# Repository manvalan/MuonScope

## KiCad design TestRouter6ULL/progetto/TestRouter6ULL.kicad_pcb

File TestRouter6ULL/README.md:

# TestRouter6ULL: scheda minima i.MX 6ULL + DDR3L per provare lo sbroglio con BoardLab

Scheda di prova **solo placement, nessuna pista**: tutte le connessioni sono lasciate all'autorouter. Aprire `progetto/TestRouter6ULL.kicad_pro`.

| | |
|---|---|
| Scheda | 60 x 50 mm, angoli raggiati 3 mm, 4 fori M2 con keepout |
| Strati | 4 (F.Cu, In1.Cu GND, In2.Cu PWR, B.Cu), stackup standard PCBWay come ProvaDDR |
| Componenti | 89 (65 top, 24 bottom) + 4 fori |
| Net | 84 (44 classe `DDR`, 6 classe `DDR_DIFF`, 34 `Default`) |
| ERC | 0 errori, 0 avvisi |
| DRC | 0 violazioni, 0 problemi di parita' schema/PCB, 349 connessioni non sbrogliate (attese) |

File: `schema-testrouter6ull.pdf` (schema), `placement-testrouter6ull.png` (top a sinistra, bottom specchiato a destra).

## Contenuto

- **U1** NXP MCIMX6Y2CVM08AB, MAPBGA-289 14x14 passo 0.8. Mappa delle sfere da SchedaIMX6ULL-SD (IMX6ULLCEC Rev 1.2, tabelle 90/91). Collegati solo DDR, alimentazioni, clock, reset, boot e UART1; le altre sfere hanno il no_connect.
- **U2** Micron MT41K512M16HA-107:A, DDR3L x16 1 GB, FBGA-96 9x14 passo 0.8. **AS4C512M16D3LC non c'e' nella libreria MIKILAB**: uso il Micron, stessa ball map JEDEC x16 e stesso footprint, quindi si puo' montare l'Alliance senza modifiche. Simbolo: MT41K256M16HA di KiCad con A15 su M7.
- Bus DDR completo SoC-DRAM: DQ0-15, LDQS/UDQS P/N, LDM/UDM, A0-A15, BA0-2, CK P/N, CKE, CS#, RAS#, CAS#, WE#, ODT, RESET#. ZQ 240R 1% su SoC e DRAM, VREF a partitore 1k/1k con 100 nF su ogni resistenza (unica per DRAM_VREF, VREFCA, VREFDQ), 10k a GND su RESET# e CKE, 100R tra CK_P e CK_N vicino alla DRAM.
- Disaccoppiamento di SoC e DDR come SchedaIMX6ULL-SD, tutto 0603 o piu' grande: 17 condensatori sul bottom sotto e accanto alle BGA (8 sotto U1, 4 sotto U2, 5 sui rail `_CAP` vicino all'angolo basso destro di U1).
- Y1 24 MHz (X322524MOB4SI) con 2x18 pF, Y2 32.768 kHz (Q13FC1350000400) con 2x12 pF, sotto il SoC vicino alle sfere XTAL e RTC.
- POR_B: RC 10k/1uF dal 3.3 V. JTAG_MOD 4.7k a GND, JTAG non usato.
- BOOT_MODE[1:0] = 01 (serial downloader, la scheda non ha memorie di boot: il ROM aspetta su UART1/USB). Due resistenze DNP per passare a BOOT_MODE = 10.
- J2 console UART1 (header 3 pin: TX, RX, GND) sul bordo alto.

## Alimentazione

Scelta la soluzione con i regolatori sulla scheda (gli stessi, con gli stessi valori, di SchedaIMX6ULL-SD) invece dei rail da header: e' poco piu' complessa e la scheda resta alimentabile da sola con 5 V.

- J1 header 2 pin: 5 V e GND, sul bordo basso.
- U3 TPS563201 -> 3V3 (FB 33.2k/10k), primo della sequenza.
- U4 TLV62569 -> V1P35 per NVCC_DRAM e DDR3L (FB 150k/120k), EN 100k/470nF dal 3V3.
- U5 TLV62569 -> V1P4 per VDD_SOC_IN (FB 133k/100k = 1.398 V), EN 100k/1uF dal 3V3.
- VDD_SNVS_IN e VDD_HIGH_IN dal 3V3, niente pila.

I buck sono in colonna sul lato destro, lontani dalla DDR3L.

## Regole e classi

Stackup PCBWay 4 strati 1.6 mm (voce 1 della tabella *Multi-layer laminated structure*): prepreg 7628 0.1855 mm Er 4.74, core 1.03 mm, rame 1 oz su tutti gli strati. Identico a ProvaDDR.

Regole in `progetto/TestRouter6ULL.kicad_dru`: piste 5 mil (0.127 mm), 4 mil (0.1016 mm) sotto il courtyard di qualsiasi componente su entrambi i lati, distanza 0.1 mm, via 0.45/0.2 mm.

| Classe | Net | Pista | Distanza | Coppia |
|---|---|---|---|---|
| `DDR` | A, BA, DQ, DM e comandi (44) | 0.127 | 0.127 | |
| `DDR_DIFF` | CK, LDQS, UDQS (6) | 0.127 | 0.127 | 0.127 / gap 0.127 |
| `Default` | il resto, VREF e ZQ compresi | 0.127 | 0.1 | |

Le classi DDR sono a 5 mil, non a impedenza controllata: su questo stackup 5 mil sono circa 77 ohm singola (calcolo di ProvaDDR), 50 ohm richiederebbe 0.316 mm, che non passano tra le sfere. Per una scheda di prova dello sbroglio e' la scelta piu' semplice; per una scheda vera serve uno stackup con prepreg sottile.

## Rigenerazione

`generatori/build.sh` rigenera tutto in `progetto/` (schema, ERC, PDF, PCB, DRC, PNG). Serve KiCad 10 con il modulo Python `pcbnew`, le librerie standard di KiCad 10 e la libreria MIKILAB (`~/Develop/mikilab-kicad-library` o variabile `MIKILAB`). I generatori sono adattati da `SchedaIMX6ULL-SD/generatori` (branch `claude/project-thread-034nik`). Le posizioni dei passivi sono calcolate: ogni rigenerazione puo' spostarli di poco.

## Problemi aperti

- AS4C512M16D3LC assente dalla libreria: in schema c'e' MT41K512M16HA (compatibile pin a pin).
- Alcuni passivi lenti del SoC (boot, POR, bulk 22 uF) sono a 13-17 mm da U1, perche' la corona attorno alle BGA resta libera per il fanout.
- I resistori VREF/ZQ della DRAM sono nell'angolo basso sinistro, a 10-16 mm da U2: vanno bene per la prova del router, su una scheda vera ZQ e VREF vanno avvicinati.
- I condensatori sul bottom sotto le BGA occupano posti dove uno sbroglio con un via per sfera metterebbe i via di alimentazione: lo sbrogliatore dovra' condividerli o spostarli, come in ProvaDDR.

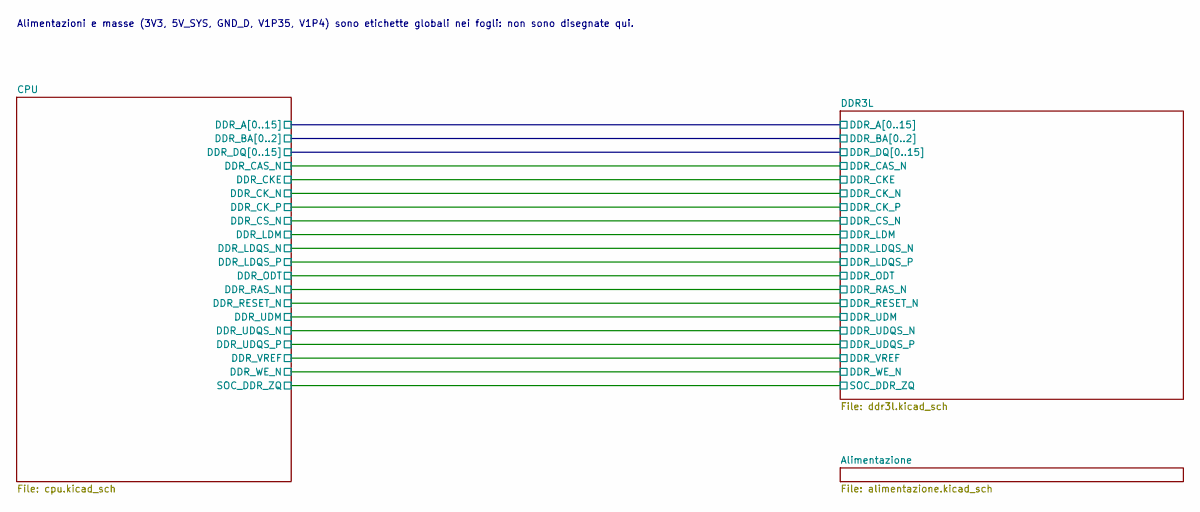
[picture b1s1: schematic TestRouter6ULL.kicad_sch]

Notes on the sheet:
Alimentazioni e masse (3V3, 5V_SYS, GND_D, V1P35, V1P4) sono etichette globali nei fogli: non sono disegnate qui.

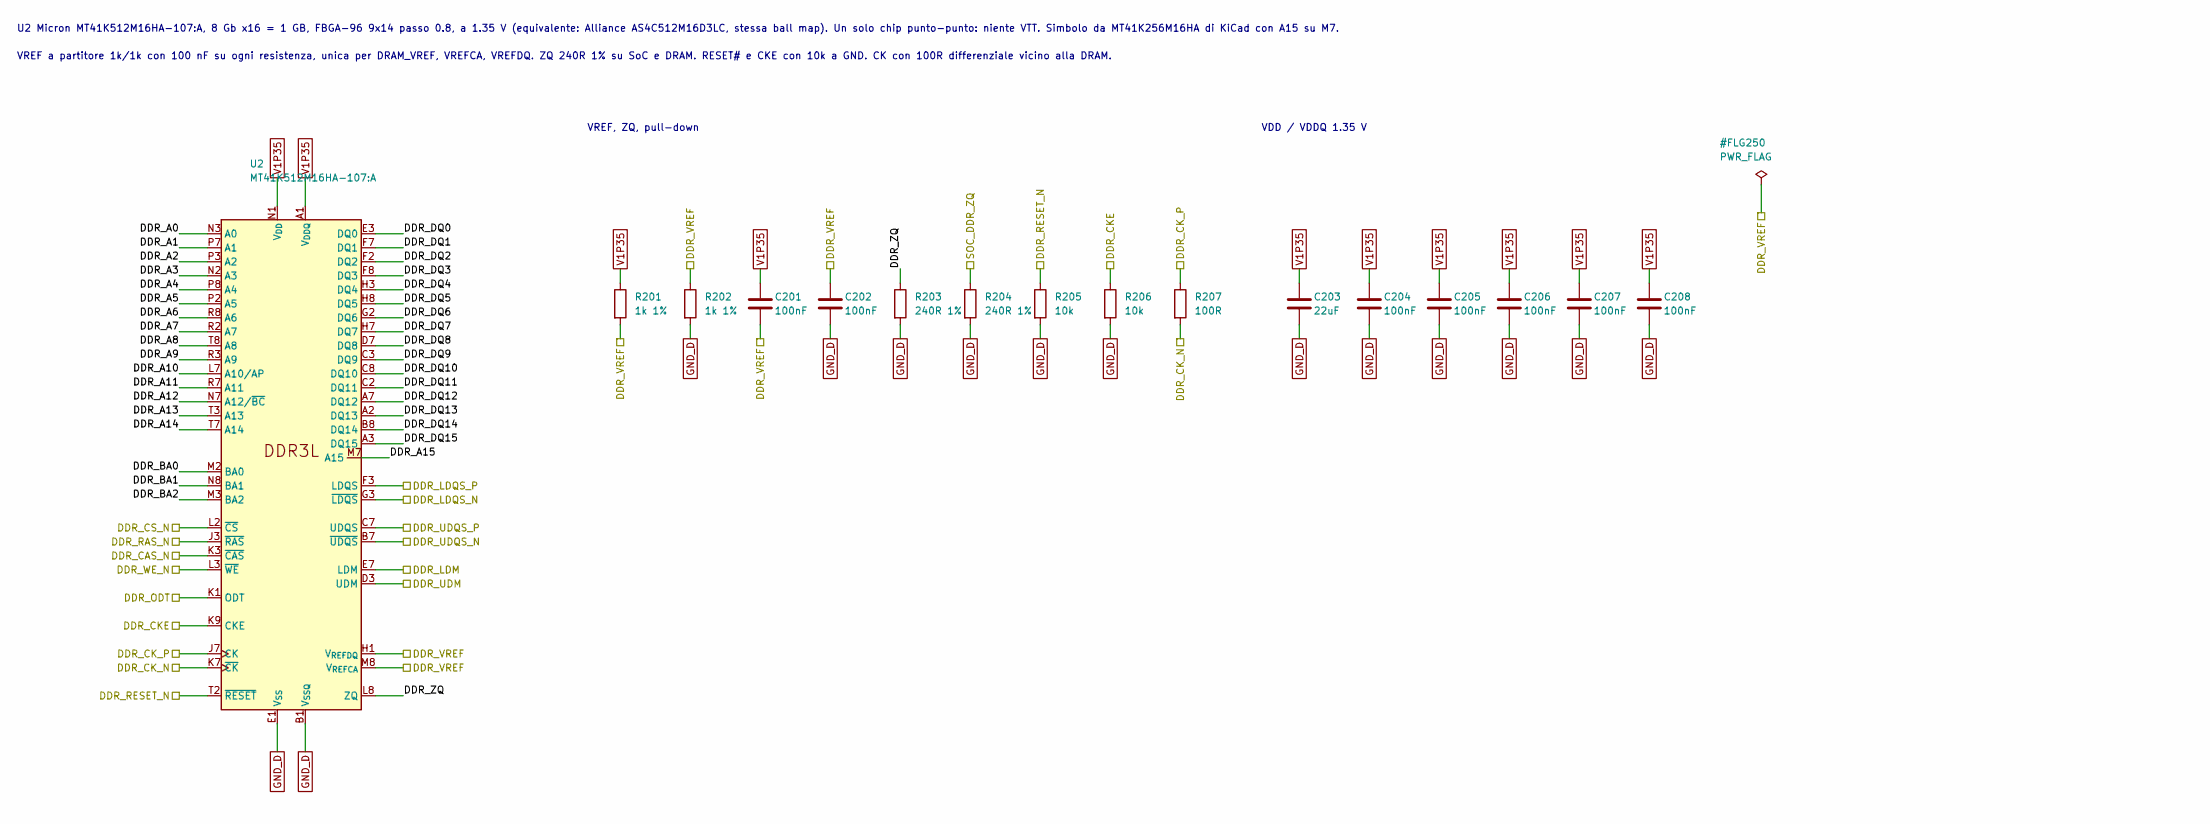
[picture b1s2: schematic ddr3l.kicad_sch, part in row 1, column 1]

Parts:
C201, C202, C204, C205, C206, C207, C208: 100nF; C_0603_1608Metric
C203: 22uF; C_0805_2012Metric
R201, R202: 1k 1%; R_0603_1608Metric
R203, R204: 240R 1%; R_0603_1608Metric
R205, R206: 10k; R_0603_1608Metric
R207: 100R; R_0603_1608Metric
U2: MT41K512M16HA-107:A; Micron_FBGA-96_9x14mm_Layout9x16_P0.8mm; MPN MT41K512M16HA-107:A

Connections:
/CPU/DDR_A0: U2.N3 (A0); also elsewhere on the board
/CPU/DDR_A1: U2.P7 (A1); also elsewhere on the board
/CPU/DDR_A2: U2.P3 (A2); also elsewhere on the board
/CPU/DDR_A3: U2.N2 (A3); also elsewhere on the board
/CPU/DDR_A4: U2.P8 (A4); also elsewhere on the board
/CPU/DDR_A5: U2.P2 (A5); also elsewhere on the board
/CPU/DDR_A6: U2.R8 (A6); also elsewhere on the board
/CPU/DDR_A7: U2.R2 (A7); also elsewhere on the board
/CPU/DDR_A8: U2.T8 (A8); also elsewhere on the board
/CPU/DDR_A9: U2.R3 (A9); also elsewhere on the board
/CPU/DDR_A10: U2.L7 (A10/AP); also elsewhere on the board
/CPU/DDR_A11: U2.R7 (A11); also elsewhere on the board
/CPU/DDR_A12: U2.N7 (A12/~BC); also elsewhere on the board
/CPU/DDR_A13: U2.T3 (A13); also elsewhere on the board
/CPU/DDR_A14: U2.T7 (A14); also elsewhere on the board
/CPU/DDR_A15: U2.M7 (A15); also elsewhere on the board
/CPU/DDR_BA0: U2.M2 (BA0); also elsewhere on the board
/CPU/DDR_BA1: U2.N8 (BA1); also elsewhere on the board
/CPU/DDR_BA2: U2.M3 (BA2); also elsewhere on the board
/CPU/DDR_CAS_N: U2.K3 (~CAS); also elsewhere on the board
/CPU/DDR_CKE: R206.1, U2.K9 (CKE); also elsewhere on the board
/CPU/DDR_CK_N: R207.2, U2.K7 (~CK); also elsewhere on the board
/CPU/DDR_CK_P: R207.1, U2.J7 (CK); also elsewhere on the board
/CPU/DDR_CS_N: U2.L2 (~CS); also elsewhere on the board
/CPU/DDR_DQ0: U2.E3 (DQ0); also elsewhere on the board
/CPU/DDR_DQ1: U2.F7 (DQ1); also elsewhere on the board
/CPU/DDR_DQ2: U2.F2 (DQ2); also elsewhere on the board
/CPU/DDR_DQ3: U2.F8 (DQ3); also elsewhere on the board
/CPU/DDR_DQ4: U2.H3 (DQ4); also elsewhere on the board
/CPU/DDR_DQ5: U2.H8 (DQ5); also elsewhere on the board
/CPU/DDR_DQ6: U2.G2 (DQ6); also elsewhere on the board
/CPU/DDR_DQ7: U2.H7 (DQ7); also elsewhere on the board
/CPU/DDR_DQ8: U2.D7 (DQ8); also elsewhere on the board
/CPU/DDR_DQ9: U2.C3 (DQ9); also elsewhere on the board
/CPU/DDR_DQ10: U2.C8 (DQ10); also elsewhere on the board
/CPU/DDR_DQ11: U2.C2 (DQ11); also elsewhere on the board
/CPU/DDR_DQ12: U2.A7 (DQ12); also elsewhere on the board
/CPU/DDR_DQ13: U2.A2 (DQ13); also elsewhere on the board
/CPU/DDR_DQ14: U2.B8 (DQ14); also elsewhere on the board
/CPU/DDR_DQ15: U2.A3 (DQ15); also elsewhere on the board
/CPU/DDR_LDM: U2.E7 (LDM); also elsewhere on the board
/CPU/DDR_LDQS_N: U2.G3 (~LDQS); also elsewhere on the board
/CPU/DDR_LDQS_P: U2.F3 (LDQS); also elsewhere on the board
/CPU/DDR_ODT: U2.K1 (ODT); also elsewhere on the board
/CPU/DDR_RAS_N: U2.J3 (~RAS); also elsewhere on the board
/CPU/DDR_RESET_N: R205.1, U2.T2 (~RESET); also elsewhere on the board
/CPU/DDR_UDM: U2.D3 (UDM); also elsewhere on the board
/CPU/DDR_UDQS_N: U2.B7 (~UDQS); also elsewhere on the board
/CPU/DDR_UDQS_P: U2.C7 (UDQS); also elsewhere on the board
/CPU/DDR_VREF: C201.2, C202.1, R201.2, R202.1, U2.H1 (V_{REFDQ}), U2.M8 (V_{REFCA}); also elsewhere on the board
/CPU/DDR_WE_N: U2.L3 (~WE); also elsewhere on the board
/CPU/SOC_DDR_ZQ: R204.1; also elsewhere on the board
/DDR3L/DDR_ZQ: R203.1, U2.L8 (ZQ)
GND_D: C202.2, C203.2, C204.2, C205.2, C206.2, C207.2, C208.2, R202.2, R203.2, R204.2, R205.2, R206.2, U2.A9 (V_{SS}), U2.B1 (V_{SSQ}), U2.B3 (V_{SS}), U2.B9 (V_{SSQ}), U2.D1 (V_{SSQ}), U2.D8 (V_{SSQ}), U2.E1 (V_{SS}), U2.E2 (V_{SSQ}), U2.E8 (V_{SSQ}), U2.F9 (V_{SSQ}), U2.G1 (V_{SSQ}), U2.G8 (V_{SS}), U2.G9 (V_{SSQ}), U2.J2 (V_{SS}), U2.J8 (V_{SS}), U2.M1 (V_{SS}), U2.M9 (V_{SS}), U2.P1 (V_{SS}), U2.P9 (V_{SS}), U2.T1 (V_{SS}), U2.T9 (V_{SS}); also elsewhere on the board
V1P35: C201.1, C203.1, C204.1, C205.1, C206.1, C207.1, C208.1, R201.1, U2.A1 (V_{DDQ}), U2.A8 (V_{DDQ}), U2.B2 (V_{DD}), U2.C1 (V_{DDQ}), U2.C9 (V_{DDQ}), U2.D2 (V_{DDQ}), U2.D9 (V_{DD}), U2.E9 (V_{DDQ}), U2.F1 (V_{DDQ}), U2.G7 (V_{DD}), U2.H2 (V_{DDQ}), U2.H9 (V_{DDQ}), U2.K2 (V_{DD}), U2.K8 (V_{DD}), U2.N1 (V_{DD}), U2.N9 (V_{DD}), U2.R1 (V_{DD}), U2.R9 (V_{DD}); also elsewhere on the board

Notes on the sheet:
U2 Micron MT41K512M16HA-107:A, 8 Gb x16 = 1 GB, FBGA-96 9x14 passo 0.8, a 1.35 V (equivalente: Alliance AS4C512M16D3LC, stessa ball map). Un solo chip punto-punto: niente VTT. Simbolo da MT41K256M16HA di KiCad con A15 su M7.
VREF a partitore 1k/1k con 100 nF su ogni resistenza, unica per DRAM_VREF, VREFCA, VREFDQ. ZQ 240R 1% su SoC e DRAM. RESET# e CKE con 10k a GND. CK con 100R differenziale vicino alla DRAM.
VREF, ZQ, pull-down
VDD / VDDQ 1.35 V

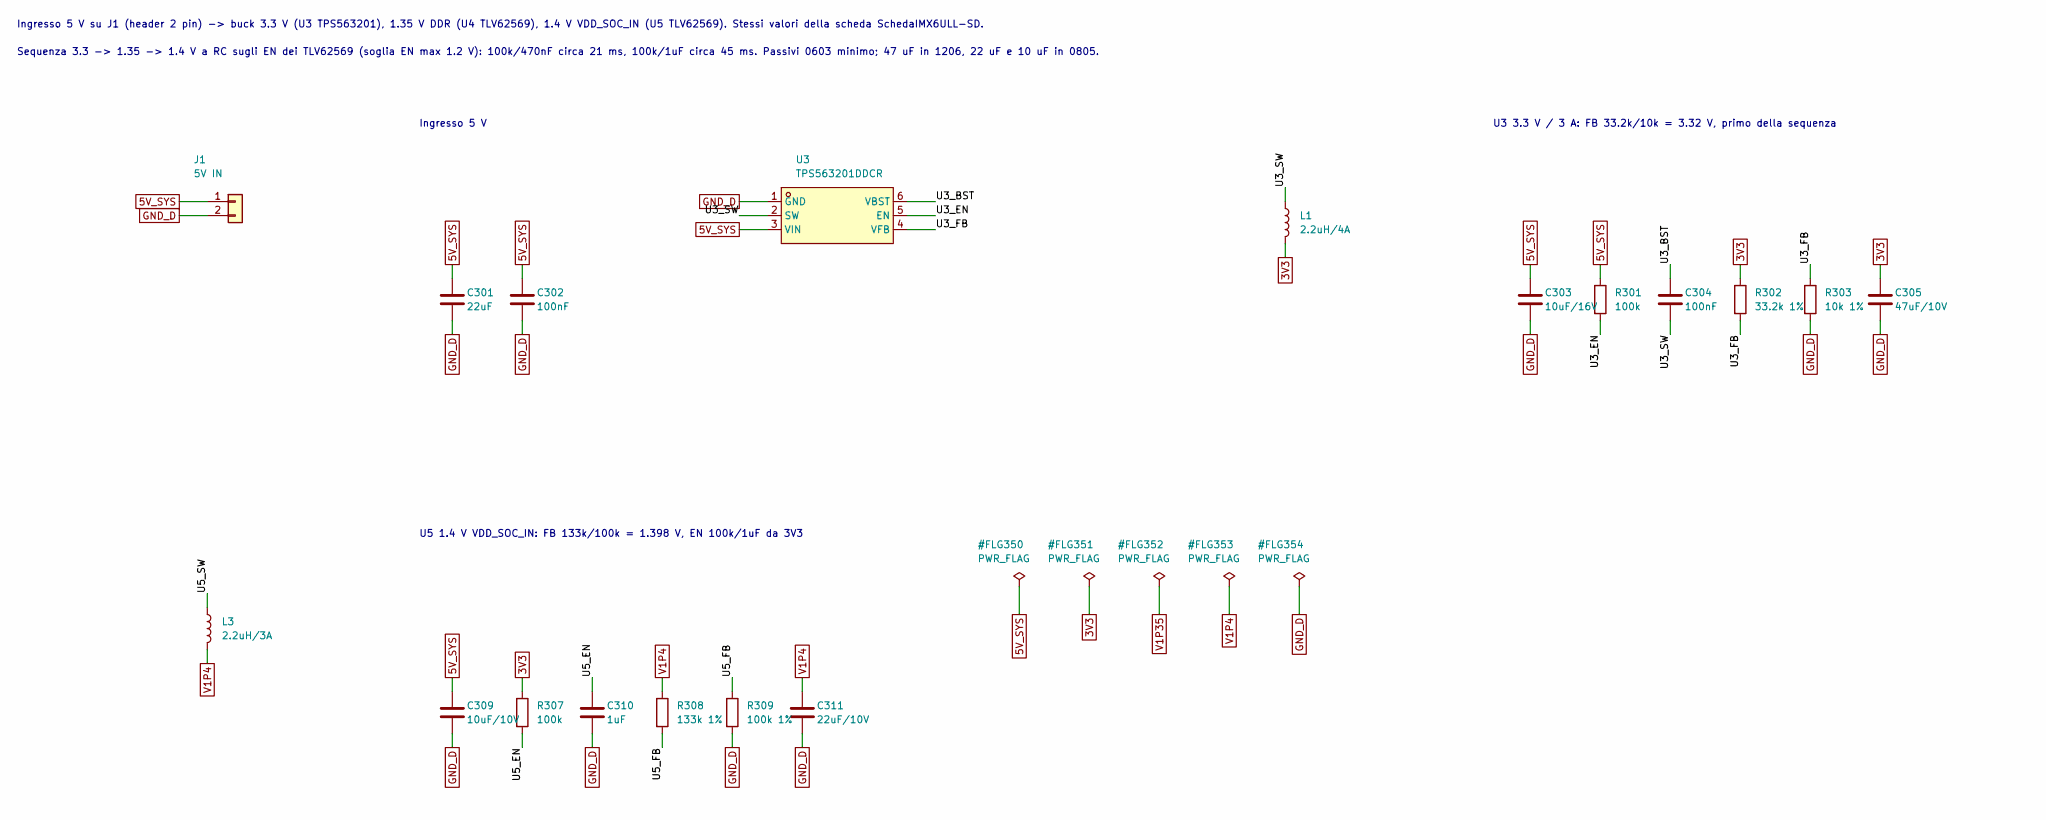
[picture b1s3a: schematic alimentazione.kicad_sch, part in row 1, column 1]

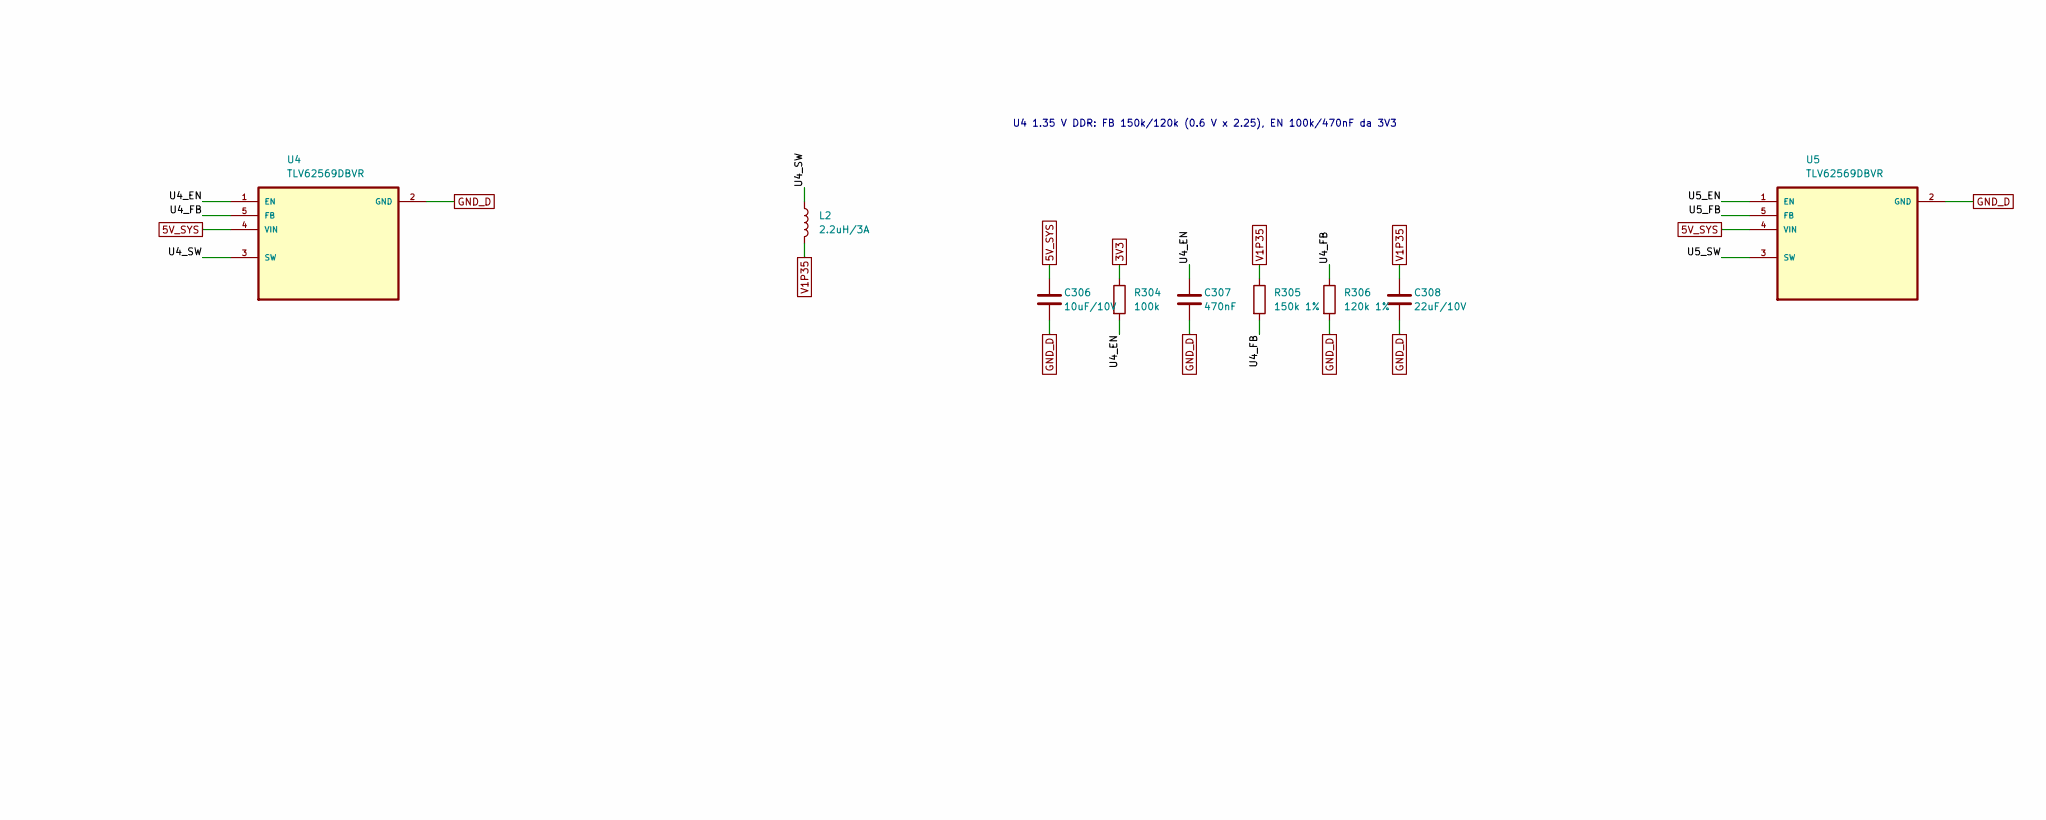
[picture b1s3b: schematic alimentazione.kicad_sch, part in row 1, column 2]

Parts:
C301: 22uF; C_1206_3216Metric
C302, C304: 100nF; C_0603_1608Metric
C303: 10uF/16V; C_0805_2012Metric
C305: 47uF/10V; C_1206_3216Metric
C306, C309: 10uF/10V; C_0805_2012Metric
C307: 470nF; C_0603_1608Metric
C308, C311: 22uF/10V; C_0805_2012Metric
C310: 1uF; C_0603_1608Metric
J1: 5V IN; PinHeader_1x02_P2.54mm_Vertical; MPN 2.54-1*2P; LCSC C49661
L1: 2.2uH/4A; L_Coilcraft_XAL4020-XXX; MPN XAL4020-222
L2, L3: 2.2uH/3A; L_Coilcraft_XAL4020-XXX; MPN XAL4020-222
R301, R304, R307: 100k; R_0603_1608Metric
R302: 33.2k 1%; R_0603_1608Metric
R303: 10k 1%; R_0603_1608Metric
R305: 150k 1%; R_0603_1608Metric
R306: 120k 1%; R_0603_1608Metric
R308: 133k 1%; R_0603_1608Metric
R309: 100k 1%; R_0603_1608Metric
U3: TPS563201DDCR; TPS563201DDCR_SOT-23-6_L2.9-W1.6-P0.95-LS2.8-BR; MPN TPS563201DDCR; LCSC C116592
U4, U5: TLV62569DBVR; TLV62569DBVR_SOT95P280X145-5N; MPN TLV62569DBVR

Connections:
3V3: C305.1, L1.2, R302.1, R304.1, R307.1; also elsewhere on the board
5V_SYS: C301.1, C302.1, C303.1, C306.1, C309.1, J1.1, R301.1, U3.3 (VIN), U4.4 (VIN), U5.4 (VIN)
/Alimentazione/U3_BST: C304.1, U3.6 (VBST)
/Alimentazione/U3_EN: R301.2, U3.5 (EN)
/Alimentazione/U3_FB: R302.2, R303.1, U3.4 (VFB)
/Alimentazione/U3_SW: C304.2, L1.1, U3.2 (SW)
/Alimentazione/U4_EN: C307.1, R304.2, U4.1 (EN)
/Alimentazione/U4_FB: R305.2, R306.1, U4.5 (FB)
/Alimentazione/U4_SW: L2.1, U4.3 (SW)
/Alimentazione/U5_EN: C310.1, R307.2, U5.1 (EN)
/Alimentazione/U5_FB: R308.2, R309.1, U5.5 (FB)
/Alimentazione/U5_SW: L3.1, U5.3 (SW)
GND_D: C301.2, C302.2, C303.2, C305.2, C306.2, C307.2, C308.2, C309.2, C310.2, C311.2, J1.2, R303.2, R306.2, R309.2, U3.1 (GND), U4.2 (GND), U5.2 (GND); also elsewhere on the board
V1P4: C311.1, L3.2, R308.1; also elsewhere on the board
V1P35: C308.1, L2.2, R305.1; also elsewhere on the board

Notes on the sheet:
Ingresso 5 V su J1 (header 2 pin) -> buck 3.3 V (U3 TPS563201), 1.35 V DDR (U4 TLV62569), 1.4 V VDD_SOC_IN (U5 TLV62569). Stessi valori della scheda SchedaIMX6ULL-SD.
Sequenza 3.3 -> 1.35 -> 1.4 V a RC sugli EN dei TLV62569 (soglia EN max 1.2 V): 100k/470nF circa 21 ms, 100k/1uF circa 45 ms. Passivi 0603 minimo; 47 uF in 1206, 22 uF e 10 uF in 0805.
Ingresso 5 V
U3 3.3 V / 3 A: FB 33.2k/10k = 3.32 V, primo della sequenza
U4 1.35 V DDR: FB 150k/120k (0.6 V x 2.25), EN 100k/470nF da 3V3
U5 1.4 V VDD_SOC_IN: FB 133k/100k = 1.398 V, EN 100k/1uF da 3V3

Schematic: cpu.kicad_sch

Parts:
C101, C104, C116, C119, C127: 22uF; C_0805_2012Metric
C102, C103, C105, C106, C107, C109, C110, C112, C113, C115, C131, C136: 1uF; C_0603_1608Metric
C108, C111, C114: 10uF; C_0805_2012Metric
C117, C118, C120, C121, C122, C123, C124, C125, C126, C128, C129, C130: 100nF; C_0603_1608Metric
C132, C133: 18pF; C_0603_1608Metric
C134, C135: 12pF; C_0603_1608Metric
J2: Console UART1; PinHeader_1x03_P2.54mm_Vertical; MPN 2.54-1*3P; LCSC C49257
R101, R102, R106: 10k; R_0603_1608Metric
R103: 4.7k; R_0603_1608Metric
R104, R105: 10k; R_0603_1608Metric; not fitted
U1: MCIMX6Y2CVM08AB; MAPBGA-289_14x14mm_Layout17x17_P0.8mm; MPN MCIMX6Y2CVM08AB
Y1: 24MHz; X322524MOB4SI_CRYSTAL-SMD_4P-L3.2-W2.5-BL; MPN X322524MOB4SI; LCSC C70590
Y2: 32.768kHz; FC-135R_L3.2-W1.5; MPN Q13FC13500004; LCSC C32346

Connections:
3V3: C119.1, C120.1, C121.1, C122.1, C123.1, C124.1, C125.1, C126.1, C131.1, R101.2, R105.2, R106.1, U1.C4 (NVCC_SD1), U1.E7 (NVCC_NAND), U1.E13 (NVCC_LCD), U1.F4 (NVCC_CSI), U1.F13 (NVCC_ENET), U1.H13 (NVCC_UART), U1.J13 (NVCC_GPIO), U1.L13 (VDDA_ADC_3P3), U1.M13 (ADC_VREFH), U1.N13 (VDD_HIGH_IN), U1.P12 (VDD_SNVS_IN); also elsewhere on the board
/CPU/BOOT_MODE0: R101.1, R104.1, U1.T10 (BOOT_MODE0)
/CPU/BOOT_MODE1: R102.1, R105.1, U1.U10 (BOOT_MODE1)
/CPU/DDR_A0: U1.L5 (DRAM_ADDR00); also elsewhere on the board
/CPU/DDR_A1: U1.H2 (DRAM_ADDR01); also elsewhere on the board
/CPU/DDR_A2: U1.K1 (DRAM_ADDR02); also elsewhere on the board
/CPU/DDR_A3: U1.M2 (DRAM_ADDR03); also elsewhere on the board
/CPU/DDR_A4: U1.K4 (DRAM_ADDR04); also elsewhere on the board
/CPU/DDR_A5: U1.L1 (DRAM_ADDR05); also elsewhere on the board
/CPU/DDR_A6: U1.G2 (DRAM_ADDR06); also elsewhere on the board
/CPU/DDR_A7: U1.H4 (DRAM_ADDR07); also elsewhere on the board
/CPU/DDR_A8: U1.J4 (DRAM_ADDR08); also elsewhere on the board
/CPU/DDR_A9: U1.L2 (DRAM_ADDR09); also elsewhere on the board
/CPU/DDR_A10: U1.M4 (DRAM_ADDR10); also elsewhere on the board
/CPU/DDR_A11: U1.K3 (DRAM_ADDR11); also elsewhere on the board
/CPU/DDR_A12: U1.L4 (DRAM_ADDR12); also elsewhere on the board
/CPU/DDR_A13: U1.H3 (DRAM_ADDR13); also elsewhere on the board
/CPU/DDR_A14: U1.G1 (DRAM_ADDR14); also elsewhere on the board
/CPU/DDR_A15: U1.K5 (DRAM_ADDR15); also elsewhere on the board
/CPU/DDR_BA0: U1.M1 (DRAM_SDBA0); also elsewhere on the board
/CPU/DDR_BA1: U1.H1 (DRAM_SDBA1); also elsewhere on the board
/CPU/DDR_BA2: U1.K2 (DRAM_SDBA2); also elsewhere on the board
/CPU/DDR_CAS_N: U1.J2 (DRAM_CAS_B); also elsewhere on the board
/CPU/DDR_CKE: U1.M3 (DRAM_SDCKE0); also elsewhere on the board
/CPU/DDR_CK_N: U1.P2 (DRAM_SDCLK0_N); also elsewhere on the board
/CPU/DDR_CK_P: U1.P1 (DRAM_SDCLK0_P); also elsewhere on the board
/CPU/DDR_CS_N: U1.N2 (DRAM_CS0_B); also elsewhere on the board
/CPU/DDR_DQ0: U1.T4 (DRAM_DATA00); also elsewhere on the board
/CPU/DDR_DQ1: U1.U6 (DRAM_DATA01); also elsewhere on the board
/CPU/DDR_DQ2: U1.T6 (DRAM_DATA02); also elsewhere on the board
/CPU/DDR_DQ3: U1.U7 (DRAM_DATA03); also elsewhere on the board
/CPU/DDR_DQ4: U1.U8 (DRAM_DATA04); also elsewhere on the board
/CPU/DDR_DQ5: U1.T8 (DRAM_DATA05); also elsewhere on the board
/CPU/DDR_DQ6: U1.T5 (DRAM_DATA06); also elsewhere on the board
/CPU/DDR_DQ7: U1.U4 (DRAM_DATA07); also elsewhere on the board
/CPU/DDR_DQ8: U1.U2 (DRAM_DATA08); also elsewhere on the board
/CPU/DDR_DQ9: U1.U3 (DRAM_DATA09); also elsewhere on the board
/CPU/DDR_DQ10: U1.U5 (DRAM_DATA10); also elsewhere on the board
/CPU/DDR_DQ11: U1.R4 (DRAM_DATA11); also elsewhere on the board
/CPU/DDR_DQ12: U1.P5 (DRAM_DATA12); also elsewhere on the board
/CPU/DDR_DQ13: U1.P3 (DRAM_DATA13); also elsewhere on the board
/CPU/DDR_DQ14: U1.R2 (DRAM_DATA14); also elsewhere on the board
/CPU/DDR_DQ15: U1.R1 (DRAM_DATA15); also elsewhere on the board
/CPU/DDR_LDM: U1.T7 (DRAM_DQM0); also elsewhere on the board
/CPU/DDR_LDQS_N: U1.P7 (DRAM_SDQS0_N); also elsewhere on the board
/CPU/DDR_LDQS_P: U1.P6 (DRAM_SDQS0_P); also elsewhere on the board
/CPU/DDR_ODT: U1.N1 (DRAM_ODT0); also elsewhere on the board
/CPU/DDR_RAS_N: U1.M5 (DRAM_RAS_B); also elsewhere on the board
/CPU/DDR_RESET_N: U1.G4 (DRAM_RESET); also elsewhere on the board
/CPU/DDR_UDM: U1.T3 (DRAM_DQM1); also elsewhere on the board
/CPU/DDR_UDQS_N: U1.T2 (DRAM_SDQS1_N); also elsewhere on the board
/CPU/DDR_UDQS_P: U1.T1 (DRAM_SDQS1_P); also elsewhere on the board
/CPU/DDR_VREF: U1.P4 (DRAM_VREF); also elsewhere on the board
/CPU/DDR_WE_N: U1.J1 (DRAM_SDWE_B); also elsewhere on the board
/CPU/JTAG_MOD: R103.1, U1.P15 (JTAG_MOD)
/CPU/NVCC_PLL: C111.1, C112.1, U1.P13 (NVCC_PLL)
/CPU/POR_B: C136.1, R106.2, U1.P8 (POR_B)
/CPU/RTC_XTALI: C134.1, U1.T11 (RTC_XTALI), Y2.1
/CPU/RTC_XTALO: C135.1, U1.U11 (RTC_XTALO), Y2.2
/CPU/SOC_DDR_ZQ: U1.N4 (DRAM_ZQPAD); also elsewhere on the board
/CPU/UART1_RX: J2.2, U1.K16 (UART1_RX_DATA)
/CPU/UART1_TX: J2.1, U1.K14 (UART1_TX_DATA)
/CPU/VDD_ARM_CAP: C101.1, C102.1, C103.1, U1.G9 (VDD_ARM_CAP), U1.G10 (VDD_ARM_CAP), U1.G11 (VDD_ARM_CAP), U1.H11 (VDD_ARM_CAP)
/CPU/VDD_HIGH_CAP: C108.1, C109.1, C110.1, U1.N6 (NVCC_DRAM_2P5), U1.R14 (VDD_HIGH_CAP), U1.R15 (VDD_HIGH_CAP)
/CPU/VDD_SNVS_CAP: C113.1, U1.N12 (VDD_SNVS_CAP)
/CPU/VDD_SOC_CAP: C104.1, C105.1, C106.1, C107.1, U1.G8 (VDD_SOC_CAP), U1.H8 (VDD_SOC_CAP), U1.J8 (VDD_SOC_CAP), U1.J11 (VDD_SOC_CAP), U1.K8 (VDD_SOC_CAP), U1.K11 (VDD_SOC_CAP), U1.L8 (VDD_SOC_CAP), U1.L9 (VDD_SOC_CAP), U1.L10 (VDD_SOC_CAP), U1.L11 (VDD_SOC_CAP)
/CPU/VDD_USB_CAP: C114.1, C115.1, U1.R12 (VDD_USB_CAP)
/CPU/XTALI: C132.1, U1.T16 (XTALI), Y1.1 (OSC1)
/CPU/XTALO: C133.1, U1.T17 (XTALO), Y1.3 (OSC2)
GND_D: C101.2, C102.2, C103.2, C104.2, C105.2, C106.2, C107.2, C108.2, C109.2, C110.2, C111.2, C112.2, C113.2, C114.2, C115.2, C116.2, C117.2, C118.2, C119.2, C120.2, C121.2, C122.2, C123.2, C124.2, C125.2, C126.2, C127.2, C128.2, C129.2, C130.2, C131.2, C132.2, C133.2, C134.2, C135.2, C136.2, J2.3, R102.2, R103.2, R104.2, U1.A1 (VSS), U1.A17 (VSS), U1.C3 (VSS), U1.C7 (VSS), U1.C11 (VSS), U1.C15 (VSS), U1.E8 (VSS), U1.E11 (VSS), U1.F6 (VSS), U1.F7 (VSS), U1.F8 (VSS), U1.F9 (VSS), U1.F10 (VSS), U1.F11 (VSS), U1.F12 (VSS), U1.G3 (VSS), U1.G5 (VSS), U1.G7 (VSS), U1.G12 (VSS), U1.G15 (VSS), U1.H7 (VSS), U1.H12 (VSS), U1.J5 (VSS), U1.J7 (VSS), U1.J12 (VSS), U1.K7 (VSS), U1.K12 (VSS), U1.L3 (VSS), U1.L7 (VSS), U1.L12 (VSS), U1.M7 (VSS), U1.M8 (VSS), U1.M9 (VSS), U1.M10 (VSS), U1.M11 (VSS), U1.M12 (NGND_KEL0), U1.N3 (VSS), U1.N5 (VSS), U1.N7 (TEST_MODE), U1.R3 (VSS), U1.R5 (VSS), U1.R7 (VSS), U1.R11 (VSS), U1.R16 (VSS), U1.R17 (VSS), U1.T14 (VSS), U1.U1 (VSS), U1.U14 (VSS), U1.U17 (VSS), Y1.2 (GND), Y1.4 (GND); also elsewhere on the board
V1P4: C116.1, C117.1, C118.1, U1.H9 (VDD_SOC_IN), U1.H10 (VDD_SOC_IN), U1.J9 (VDD_SOC_IN), U1.J10 (VDD_SOC_IN), U1.K9 (VDD_SOC_IN), U1.K10 (VDD_SOC_IN); also elsewhere on the board
V1P35: C127.1, C128.1, C129.1, C130.1, U1.G6 (NVCC_DRAM), U1.H6 (NVCC_DRAM), U1.J6 (NVCC_DRAM), U1.K6 (NVCC_DRAM), U1.L6 (NVCC_DRAM), U1.M6 (NVCC_DRAM); also elsewhere on the board

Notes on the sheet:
U1 NXP MCIMX6Y2CVM08AB (i.MX 6ULL, MAPBGA-289 14x14 mm passo 0.8). Scheda di prova per lo sbroglio: collegati solo DDR3L, alimentazioni, clock, reset, boot e console UART1.
Boot: BOOT_MODE[1:0]=01 (serial downloader, la scheda non ha memorie di boot): il ROM resta in attesa su UART1/USB. R105/R106 DNP per BOOT_MODE=10 (boot interno).
POR_B: RC 10k/1uF dal 3.3 V (circa 10 ms). JTAG non usato: JTAG_MOD a GND con 4.7k (tabella 3).
VDD_ARM_CAP / VDD_SOC_CAP: uscite LDO interni, solo condensatori
VDD_HIGH_CAP (a NVCC_DRAM_2P5), NVCC_PLL, VDD_SNVS_CAP, VDD_USB_CAP
VDD_SOC_IN 1.4 V
VDD_HIGH_IN e NVCC 3.3 V: un 100 nF per dominio (CSI, ENET, GPIO, LCD, NAND, SD1, UART)
NVCC_DRAM 1.35 V (lato SoC)
VDD_SNVS_IN
Carico 24 MHz (CL da verificare sul quarzo YXC)
Carico RTC: circa 2xCL meno parassite (datasheet, tabella 3)
Boot: BOOT_MODE=01 serial downloader; le due DNP danno BOOT_MODE=10; JTAG_MOD a GND con 4.7k
POR_B: RC 10k/1uF

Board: 4 copper layers, 93 parts (24 on the bottom side), 84 nets, no tracks yet.

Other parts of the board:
H1, H2, H3, H4: MountingHole_2.2mm_M2

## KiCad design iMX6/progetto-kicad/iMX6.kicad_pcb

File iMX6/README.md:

# iMX6: scheda i.MX 6ULL derivata da nanoberry

Derivata da **nanoberry** di **vpecanins** ([github.com/EnzoRF/nanoberry](https://github.com/EnzoRF/nanoberry), commit 63c6836, 2020-06-13), **GPLv3**: vedi `LICENSE`. Copyright (C) 2020 vpecanins per il progetto originale. L'autore chiede di essere avvisato se la scheda viene prodotta o modificata: **va avvisato da Michele**.

Il progetto originale, intatto (KiCad 5), è in `nanoberry-originale/`.

## Cosa cambia rispetto a nanoberry

| | nanoberry | iMX6 |
|---|---|---|
| RAM | DDR3L 512 MB (W634GU6MB) | **DDR3L 1 GB** Alliance AS4C512M16D3LC-12BIN, FBGA-96 9x13, stessa griglia; A15 era già collegata e sbrogliata |
| Display | connettore RGB P2 + touch J6 | tolti |
| Espansione | header 2x20 P1 | tolto: i suoi pad CSI/UART servono ai bus |
| USB | hub USB2514B, 2 USB-A, micro-USB OTG, micro-USB debug con CP2102N | **USB-C 1** alimentazione + OTG1 (boot seriale), **USB-C 2 host** su USB_OTG2 con TPS2553, affiancate sul bordo destro |
| Console | CP2102N | header UART1 1x3 (J10) |
| Alimentazione | USB a diodi + LiPo con boost MIC2877 | **BUS_POWER 12 V -> TPS56637 5 V -> TPS2121** (priorità) con la USB-C 1; PF1550, LiPo e boost restano |
| Bus | - | **MIKILAB**: BUS_POWER 30 pin (ECSPI4 sui pad ENET2) e MAIN 28 pin (ECSPI1 sui pad CSI_DATA04-07, I2C1 sui pad UART4, ADDR/PREFIX/ALERT#/HIT# su UART3/UART5/CSI) con ESD |
| Radio | - | **Wi-Fi/BT BL-M8723DS1** su uSDHC2 (pad CSI) e UART2, LDO dedicato, U.FL |
| Scheda | 85 x 56 mm | **85 x 60 mm**, 4 strati: +4 mm in alto per i connettori MIKILAB |

Restano come in nanoberry: i.MX 6ULL, PMIC PF1550, QSPI (2 x W25M512JV), microSD, Ethernet LAN8720A + RJ45, A71CH, JTAG, pila. Strap di boot: i pad LCD_DATA restano liberi.

## Contenuto

| Percorso | Cosa |
|---|---|
| `progetto-kicad/iMX6.kicad_pro` | Progetto KiCad 10 |
| `schema-imx6.pdf` | Schema (12 fogli) |
| `pcb-imx6.pdf`, `.png` | PCB, top e bottom |
| `generatori/` | `converti.py` (schema dalla netlist di nanoberry + modifiche), `aggiorna_pcb.py` (PCB), `build.sh` |
| `nanoberry-originale/` | Progetto originale KiCad 5 |

## Come è stato fatto

KiCad 10 da riga di comando non legge i fogli KiCad 5 di nanoberry, quindi lo schema è **ricostruito dalla netlist originale** (`nano.net`) e dai simboli della sua cache convertiti. Il disegno è a etichette, non quello originale. Il PCB è quello di nanoberry convertito:
- tolti i 43 componenti eliminati e le 821 piste e via che portavano a loro;
- **tutte le altre piste restano come in nanoberry**, comprese DDR e fanout del SoC (nessuna net DDR cambiata);
- i 74 componenti nuovi sono **solo piazzati**, senza piste;
- i 2 fori di fissaggio in alto spostati negli angoli nuovi, quello in basso a sinistra è già nell'angolo, quello in basso a destra resta dov'era perché l'angolo è dell'RJ45.

## Stato e punti aperti

- **ERC 0** (con i tipi dei pin di nanoberry corretti: molti pin bidirezionali erano marcati input).
- **Parità schema/PCB: 0 errori di footprint.**
- **DRC: 1376 violazioni, da rivedere in KiCad.** Su questa macchina il riempimento delle zone di KiCad 10 si blocca (anche sul PCB di nanoberry non modificato), quindi le zone sono **senza riempimento**: aprire il PCB e premere B. Nel conteggio:
  - 199 via di nanoberry da 0.3/0.254 mm: corona di 0.023 mm, **da verificare col produttore**;
  - via e piste "appese" e 499 collegamenti mancanti: in parte zone non riempite, in parte componenti nuovi non sbrogliati;
  - testi e serigrafie di nanoberry sotto i minimi;
  - **14 sovrapposizioni di courtyard, 3 clearance, 4 fori troppo vicini, 2 ponti di maschera: da controllare a mano**.
- **BOOST_EN del MIC2877 è flottante anche in nanoberry** (net con un solo pin): va collegato o forzato.
- **U-Boot**: il setup DDR (DCD e calibrazione) cambia per 1 GB e 8 Gb.
- Segnali Wi-Fi e USB host su pad SNVS_TAMPER (BT_HOST_WAKE, USB2_OC_N): dominio VDD_SNVS, livelli da verificare.
- Il modulo Wi-Fi è sul bottom, l'U.FL sul top.

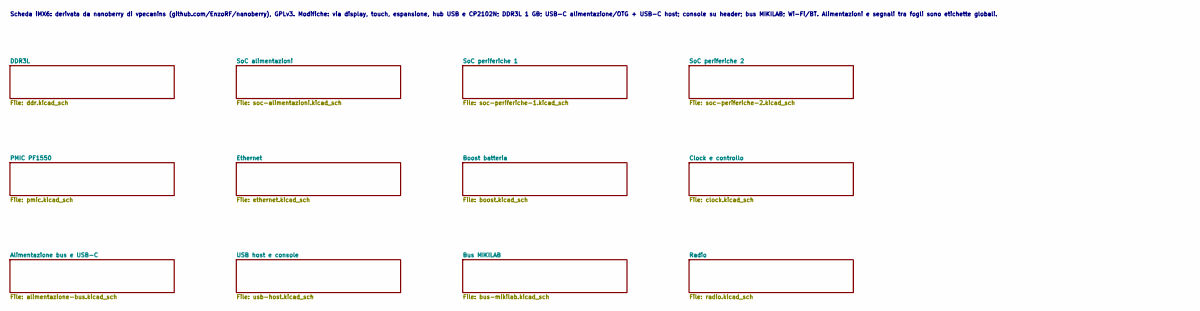
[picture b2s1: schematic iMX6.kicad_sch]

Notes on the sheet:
Scheda iMX6: derivata da nanoberry di vpecanins (github.com/EnzoRF/nanoberry), GPLv3. Modifiche: via display, touch, espansione, hub USB e CP2102N; DDR3L 1 GB; USB-C alimentazione/OTG + USB-C host; console su header; bus MIKILAB; Wi-Fi/BT. Alimentazioni e segnali tra fogli sono etichette globali.
